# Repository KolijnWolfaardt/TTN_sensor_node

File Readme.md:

# TTN Sensor Board

This is a basic sensor board I designed to experiment with the LORAWAN protocol, and [The Things Network](https://www.thethingsnetwork.org/) infrastructure. It is by no means intended to be a good or complete example of all the capabilities of either.

The board uses a Microchip RN2483 to perform the RF communication and a PIC18F46J50 for the other work. The sensors were chosen based on what was available, for experimentation. Other sensors can easily be used.

The board is powered by a single LiPo battery, which is regulated down to 3.3v. To charge the LiPo battery, A MCP73831/2 Battery Management IC is used. The power part is not finished yet, as the batteries have not arrived, so there might be updates here.

## Datasheets
* Microcontroller [PIC18F26J50](http://ww1.microchip.com/downloads/en/DeviceDoc/39931d.pdf)
* Lora Interface module [RN2483](http://ww1.microchip.com/downloads/en/DeviceDoc/50002346A.pdf)
* Battery Management IC [MCP73831/2](http://ww1.microchip.com/downloads/en/DeviceDoc/20001984g.pdf)
* Low dropout Voltage Regulator [TPS736](http://www.ti.com/lit/ds/symlink/tps736.pdf)
* Ambient Light Sensor [BH1603FVC](http://rohmfs.rohm.com/en/products/databook/datasheet/ic/sensor/light/bh1603fvc-e.pdf)
* Thermistor [MCP9701/9701A](http://ww1.microchip.com/downloads/en/DeviceDoc/21942e.pdf)
* P-channel MOSFET [NXP BSS84](http://www.nxp.com/documents/data_sheet/BSS84.pdf)
* N-channel MOSFET [NXP 2N7002](https://www.nxp.com/documents/data_sheet/2N7002.pdf)

Thanks to [https://github.com/jpmeijers/RN2483shield](https://github.com/jpmeijers/RN2483shield) for the RN2483 component and module.

## Schematic and PCB layout
The schematic and PCB layout were created using KiCad, and can be found in the **PCB Layout** folder. The gerber files and schematic PDF can also be found there.

## Firmware
The firmware can be found in the Firmware folder, and is intended for the [XC8](http://www.microchip.com/mplab/compilers) compiler using the [MPLABX](http://www.microchip.com/mplab/mplab-x-ide) IDE. The board is programmed with a PicKIT 3 programmer, but the PicKIT 2 should also work. The basic flow of the program is shown in basic_control_flow.dia (Open with [http://dia-installer.de/](Dia) flowchart editor) inside the Firmware folder.

[comment]: #  (For more details on the software, see [Firmware/README.md](Firmware/README.md) )

The radio connects via ABP (Activation by personalization). The keys were programmed beforehand using a USB-serial converter, and the radio stores them internally. I will add some code later to set them in the code.

USB stack adapted from [https://github.com/signal11/m-stack.git](https://github.com/signal11/m-stack.git), for its license see the LICENSE file.

[comment]: # (Bill of Materials)

## Board Mistakes
There are two mistakes on the board:
* The ground pin on the PicKit header is not connected.
* The battery voltage measurement circuit does not work. I replaced it with a voltage divider.

These are suggestions that require more rework, but are only for ease of use.
* I cannot identify pin 1 of the optical sensor, so I left it off.
* Breaking out the TX and RX lines to the RF module would have eased debugging.
* A reset button would be nice, resetting both the MCU and the RF module.

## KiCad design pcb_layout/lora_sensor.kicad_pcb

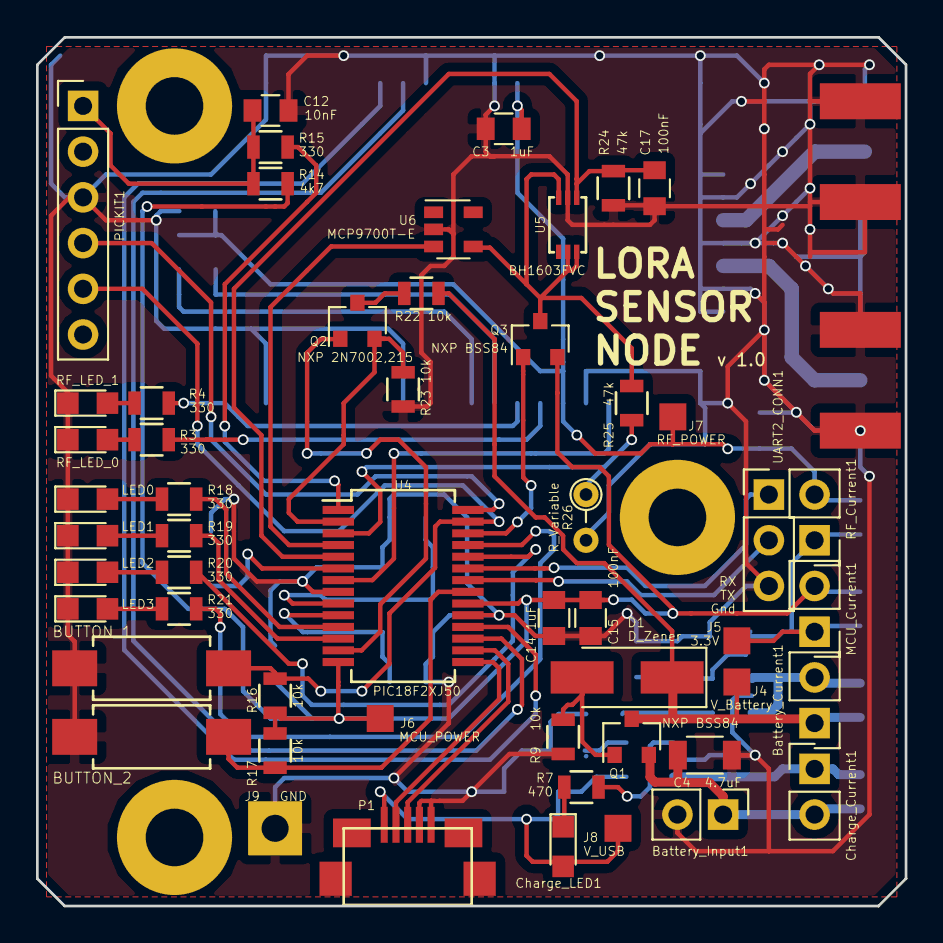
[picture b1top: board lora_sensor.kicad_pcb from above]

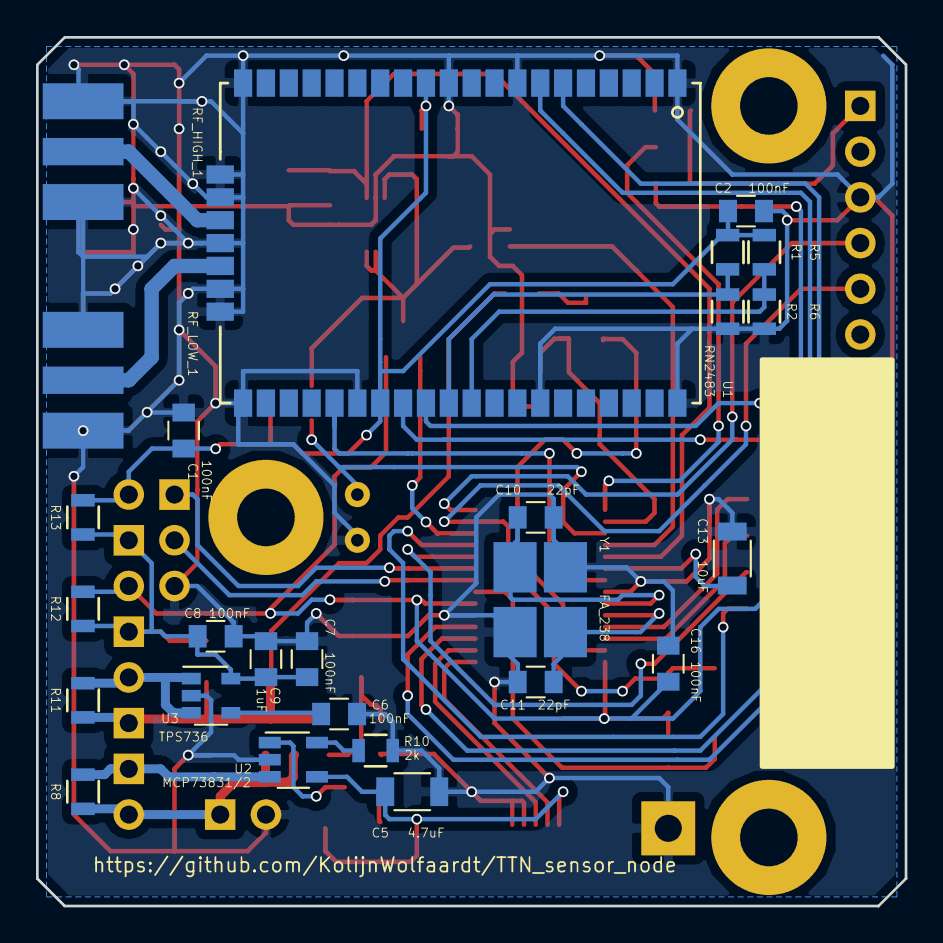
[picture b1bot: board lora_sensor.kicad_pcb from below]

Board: 2 copper layers, 48.3 x 48.3 mm, 82 parts (26 on the bottom side), 53 nets.

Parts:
BUTTON_1, BUTTON_2: SwitchTactile; SW_SPST_REED_CT05-XXXX-G1
Battery_Current1: CONN_01X02; Pin_Header_Straight_1x02_Pitch2.54mm
Battery_Input1: CONN_01X02; Pin_Header_Straight_1x02_Pitch2.54mm
C1, C2, C6, C7, C8, C15, C16, C17: 100nF; C_0805
C3, C9, C14: 1uF; C_0805
C4, C5: 4.7uF; C_1206
C10, C11: 22pF; C_0805
C12: 10nF; C_0805
C13: 10uF; C_1206
Charge_Current1: CONN_01X02; Pin_Header_Straight_1x02_Pitch2.54mm
Charge_LED1: LED; LED_0805
D1: D_Zener; D_SMA_Handsoldering
J1, J2, J3: CONN_01X01; MountingHole_3.2mm_M3_Pad
J4: V_Battery; Measurement_Point_Square-SMD-Pad_Small
J5: 3.3V; Measurement_Point_Square-SMD-Pad_Small
J6: MCU_POWER; Measurement_Point_Square-SMD-Pad_Small
J7: RF_POWER; Measurement_Point_Square-SMD-Pad_Small
J8: V_USB; Measurement_Point_Square-SMD-Pad_Small
J9: GND; Measurement_Point_Square-TH_Big
LED0, LED1, LED2, LED3: LED; LED_0805
MCU_Current1: CONN_01X02; Pin_Header_Straight_1x02_Pitch2.54mm
P1: USB_A; USB_Micro
PICKIT1: CONN_01X06; Pin_Header_Straight_1x06_Pitch2.54mm
Q1, Q3: NXP BSS84; SOT-23
Q2: NXP 2N7002,215; SOT-23
R1, R2, R5, R6, R8, R11, R12, R13: 0; R_0805
R3, R4, R15, R18, R19, R20, R21: 330; R_0805
R7: 470; R_0805
R9, R16, R17, R22, R23: 10k; R_0805
R10: 2k; R_0805
R14: 4k7; R_0805
R24, R25: 47k; R_0805
R26: R_Variable; R_Axial_DIN0204_L3.6mm_D1.6mm_P2.54mm_Vertical
RF_Current1: CONN_01X02; Pin_Header_Straight_1x02_Pitch2.54mm
RF_HIGH_1: CONN_01X02; SMA_edge_connect
RF_LED_0, RF_LED_1: LED; LED_0805
RF_LOW_1: CONN_01X02; SMA_edge_connect
U1: RN2483
U2: MCP73831/2; TSOT-23-5
U3: TPS736; SOT-23-5
U4: PIC18F2XJ50; SSOP-28_5.3x10.2mm_Pitch0.65mm
U5: BH1603FVC
U6: MCP9700T-E; SOT-23-5
UART2_CONN1: CONN_01X03; Pin_Header_Straight_1x03_Pitch2.54mm
Y1: FA_238; Crystal_FA-238

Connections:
+3V3: C7.1, C8.1, C9.1, J5.1, MCU_Current1.1, R12.2, R13.2, RF_Current1.1, U3.5
/microcontroller/AN0_Battery: Q2.2, R23.1, U4.2
/microcontroller/AN1_LDR: R25.2, R26.1, U4.3
/microcontroller/AN2_Ambient: C17.1, R24.1, U4.5, U5.1
/microcontroller/AN3_Temperature: U4.4, U6.3
/microcontroller/BUTTON_0: BUTTON_2.1, R17.2, U4.21
/microcontroller/BUTTON_1: BUTTON_1.1, PICKIT1.5, R16.2, U4.27
/microcontroller/LED0: R18.1, U4.11
/microcontroller/LED1: R19.1, U4.12
/microcontroller/LED2: R20.1, U4.24
/microcontroller/LED3: R21.1, U4.25
/microcontroller/MCU_Power: C14.1, C15.1, C16.1, J6.1, MCU_Current1.2, Q3.2, R12.1, R14.1, R16.1, R17.1, U4.14, U4.20
/microcontroller/OSC1: C10.1, U4.9, Y1.1
/microcontroller/OSC2: C11.1, U4.10, Y1.3
/microcontroller/PGD: PICKIT1.4, U4.28
/microcontroller/RF_Reset: U1.32, U4.7
/microcontroller/Sensors_Enable: Q3.1, U4.26
/microcontroller/UART_2_RX: U4.23, UART2_CONN1.1
/microcontroller/UART_2_TX: U4.22, UART2_CONN1.2
/microcontroller/USB_D+: P1.3, U4.16
/microcontroller/USB_D-: P1.2, U4.15
/microcontroller/VB_Control: Q2.1, U4.13
/microcontroller/VPP/~MCLR: C12.1, PICKIT1.1, R14.2, R15.2
/microcontroller/V_CAP: C13.1, U4.6
/microcontroller/V_USB: C5.1, Charge_LED1.2, J8.1, P1.1, U2.4
/power_section/Battery_input: Battery_Input1.1, C4.1, Charge_Current1.2, Q1.2, R8.2
/power_section/RF_Power: C1.1, C2.1, C3.1, J7.1, R1.1, R5.1, R13.1, RF_Current1.2, U1.12, U1.34
/power_section/V_Battery: Battery_Current1.1, D1.1, J4.1, Q1.3, R11.2, R22.1
/rf_section/RF_LED_0: R3.1, U1.35
/rf_section/RF_LED_1: R4.1, U1.36
/rf_section/RF_Setting_0: R1.2, R2.1, U1.37
/rf_section/RF_Setting_1: R5.2, R6.1, U1.38
/rf_section/RF_UART_RX: U1.7, U4.17
/rf_section/RF_UART_TX: U1.6, U4.18
GND: BUTTON_1.2, BUTTON_2.2, Battery_Input1.2, C1.2, C2.2, C3.2, C4.2, C5.2, C6.2, C7.2, C8.2, C9.2, C10.2, C11.2, C12.2, C13.2, C14.2, C15.2, C16.2, C17.2, J9.1, LED0.1, LED1.1, LED2.1, LED3.1, P1.4, P1.5, PICKIT1.3, R2.2, R6.2, R9.2, R10.2, R23.2, R24.2, R26.2, RF_HIGH_1.2, RF_LED_0.1, RF_LED_1.1, RF_LOW_1.2, U1.1, U1.8, U1.11, U1.20, U1.21, U1.22, U1.24, U1.26, U1.27, U1.28, U1.33, U1.41, U1.47, U2.2, U3.2, U4.8, U4.19, U5.2, U6.2, UART2_CONN1.3, Y1.2, Y1.4
unnamed: Battery_Current1.2, R11.1, U3.1, U3.3
unnamed: C6.1, U3.4
unnamed: Charge_Current1.1, R8.1, U2.3
unnamed: Charge_LED1.1, R7.1
unnamed: D1.2, Q1.1, R9.1
unnamed: LED0.2, R18.2
unnamed: LED1.2, R19.2
unnamed: LED2.2, R20.2
unnamed: LED3.2, R21.2
unnamed: Q2.3, R22.2
unnamed: Q3.3, R25.1, U5.3, U5.5, U5.6, U6.4
unnamed: R3.2, RF_LED_0.2
unnamed: R4.2, RF_LED_1.2
unnamed: R7.2, U2.1
unnamed: R10.1, U2.5
unnamed: R15.1, U4.1
unnamed: RF_HIGH_1.1, U1.23
unnamed: RF_LOW_1.1, U1.25

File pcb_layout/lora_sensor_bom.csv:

Reference, Value, Footprint, Datasheet
"C1","100nF","Capacitors_SMD:C_0805",""
"C2","100nF","Capacitors_SMD:C_0805",""
"C3","1uF","Capacitors_SMD:C_0805",""
"RF_High1","CONN_01X02","libraries:SMA_edge_connect",""
"RF_Low1","CONN_01X02","libraries:SMA_edge_connect",""
"RF_LED_1","LED","LEDs:LED_0805",""
"RF_LED_0","LED","LEDs:LED_0805",""
"R4","330","Resistors_SMD:R_0805",""
"R3","330","Resistors_SMD:R_0805",""
"R5","0","Resistors_SMD:R_0805",""
"R6","0","Resistors_SMD:R_0805",""
"R1","0","Resistors_SMD:R_0805",""
"R2","0","Resistors_SMD:R_0805",""
"U1","RN2483","libraries:RN2483",""
"C7","100nF","Capacitors_SMD:C_0805",""
"C8","100nF","Capacitors_SMD:C_0805",""
"C9","1uF","Capacitors_SMD:C_0805",""
"R12","0","Resistors_SMD:R_0805",""
"R13","0","Resistors_SMD:R_0805",""
"MCU_Current1","CONN_01X02","Socket_Strips:Socket_Strip_Straight_1x02_Pitch2.54mm",""
"RF_Current1","CONN_01X02","Socket_Strips:Socket_Strip_Angled_1x02_Pitch2.54mm",""
"Battery_Input1","CONN_01X02","Socket_Strips:Socket_Strip_Straight_1x02_Pitch2.54mm",""
"R9","10k","Resistors_SMD:R_0805",""
"D1","D_Zener","Diodes_SMD:D_SMA_Handsoldering",""
"U2","MCP73831/2","TO_SOT_Packages_SMD:TSOT-23-5",""
"Power_LED1","LED","LEDs:LED_0805",""
"R7","470","Resistors_SMD:R_0805",""
"R10","2k","Resistors_SMD:R_0805",""
"U3","TPS736","TO_SOT_Packages_SMD:SOT-23-5",""
"C6","100nF","Capacitors_SMD:C_0805",""
"C4","4.7uF","Capacitors_SMD:C_0805",""
"Battery_Current1","CONN_01X02","Socket_Strips:Socket_Strip_Straight_2x01_Pitch2.54mm",""
"Charge_Current1","CONN_01X02","Socket_Strips:Socket_Strip_Straight_2x01_Pitch2.54mm",""
"Q1","NXP BSS84","TO_SOT_Packages_SMD:SOT-23",""
"C5","4.7u","Capacitors_SMD:C_0805",""
"R11","0","Resistors_SMD:R_0805",""
"R8","0","Resistors_SMD:R_0805",""
"U4","PIC18F2XJ50","Housings_SSOP:SSOP-28_5.3x10.2mm_Pitch0.65mm",""
"PICKIT1","CONN_01X06","Socket_Strips:Socket_Strip_Straight_1x06_Pitch2.54mm",""
"P1","USB_A","libraries:USB_Micro",""
"R15","330","Resistors_SMD:R_0805",""
"R14","4k7","Resistors_SMD:R_0805",""
"C12","10nF","Capacitors_SMD:C_0805",""
"C15","100nF","Capacitors_SMD:C_0805",""
"C16","100nF","Capacitors_SMD:C_0805",""
"Y1","16Mhz","Crystals:Crystal_SMD_EuroQuartz_MQ-4pin_7.0x5.0mm_HandSoldering",""
"C11","10pF","Capacitors_SMD:C_0805",""
"C10","10pF","Capacitors_SMD:C_0805",""
"C13","10uF","Capacitors_SMD:C_0805",""
"UART2_CONN1","CONN_01X03","Socket_Strips:Socket_Strip_Straight_1x03_Pitch2.54mm",""
"LED3","LED","LEDs:LED_0805",""
"LED2","LED","LEDs:LED_0805",""
"R21","330","Resistors_SMD:R_0805",""
"R20","330","Resistors_SMD:R_0805",""
"R19","330","Resistors_SMD:R_0805",""
"LED1","LED","LEDs:LED_0805",""
"LED0","LED","LEDs:LED_0805",""
"R18","330","Resistors_SMD:R_0805",""
"BUTTON_2","SwitchTactile","Buttons_Switches_SMD:SW_SPST_REED_CT05-XXXX-G1",""
"R17","10k","Resistors_SMD:R_0805",""
"BUTTON_1","SwitchTactile","Buttons_Switches_SMD:SW_SPST_REED_CT05-XXXX-G1",""
"R16","10k","Resistors_SMD:R_0805",""
"C14","1uF","Capacitors_SMD:C_0805",""
"R22","10k","Resistors_SMD:R_0805",""
"R23","10k","Resistors_SMD:R_0805",""
"R25","47k","Resistors_SMD:R_0805",""
"R26","R_Variable","Resistors_ThroughHole:R_Axial_DIN0204_L3.6mm_D1.6mm_P2.54mm_Vertical",""
"Q3","NXP BSS84","TO_SOT_Packages_SMD:SOT-23",""
"U5","BH1603FVC","",""
"R24","47k","Resistors_SMD:R_0805",""
"C17","100nF","Capacitors_SMD:C_0805",""
"U6","MCP9700T-E","TO_SOT_Packages_SMD:SOT-23-5",""
"Q2","NXP 2N7002,215","TO_SOT_Packages_SMD:SOT-23",""

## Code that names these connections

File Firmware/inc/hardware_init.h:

/* 
 * File:   hardware_init.h
 * Author: kolijn
 *
 * Created on 20 April 2017, 6:48 AM
 */

#include <xc.h>

#ifndef HARDWARE_INIT_H
#define	HARDWARE_INIT_H

#ifdef	__cplusplus
extern "C" {
#endif

void oscillator_init(void);
void hardware_setup(void);
void led_write_num(int num);
void add_char_to_usb(char data);
void add_buffer_to_usb(char buffer[], int length);

#define LED0 LATCbits.LATC0
#define LED1 LATCbits.LATC1
#define LED2 LATBbits.LATB3
#define LED3 LATBbits.LATB4

#define BAT_SENS_DISABLE LATCbits.LATC2
#define SENSORS_ENABLE LATBbits.LATB5

#define BUTTON0 PORTBbits.RB0
#define BUTTON1 PORTBbits.RB6

#define RADIO_RESET LATAbits.LATA5

typedef enum  
{
    STARTUP=1,
    INIT_HARDWARE=2,
    FIRST_RUN=3,
    WAKE_UP_RADIO=4,
    GET_MAC_STATUS=5,
    JOIN_NETWORK=6,
    SET_DR_VALUE=7,
    SEND_VALUES=8,
    SEND_VALUES_RESPONSE=9,
    GOTO_SLEEP=10,
    SLEEP=0,
    HANDLE_ISSUE=14,
    RESET_RADIO=15,
}states_t;

states_t CURRENT_STATE = STARTUP;

struct {
    unsigned int join_status : 1;
    unsigned int mac_state : 3;
} mac_state;

#ifdef	__cplusplus
}
#endif

#endif	/* HARDWARE_INIT_H */

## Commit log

2017-02-05 Added basic PCB layout
2017-02-05 Adds Readme, License and .gitignore
2017-02-05 Updates Schematic
2017-02-06 Improved schematic, updated component-module mappings
2017-02-07 More modules, initial pcb layout
2017-02-12 Added PCB LAyout
2017-02-12 Finalized layout, added gerbers and renders
2017-02-13 Small layout improvements
2017-02-13 More layout updates
2017-07-01 Manufactured version
2017-07-01 Updates Licenses
2017-07-01 Moved pcb layout folder
2017-07-01 Updates Readme, remove old license file
2017-07-01 Gitignore for Firmware
2017-07-01 Adds firmware, currently transmitting every minute
2017-07-01 Removed generated makefiles from commit
2017-07-01 Adds images, updates readme
2017-07-01 Fix links in readme?
2017-07-01 Fix images in readme?
2017-07-02 Fix images. Resized manually, added different board photo
2017-07-02 Small fix
2017-07-02 Adds missing files
2017-07-02 Minor changes to readme
2017-11-08 Firmware works without periodic crashes
2017-11-08 Updated link in readme
2017-11-08 Updated libraries to newer version
